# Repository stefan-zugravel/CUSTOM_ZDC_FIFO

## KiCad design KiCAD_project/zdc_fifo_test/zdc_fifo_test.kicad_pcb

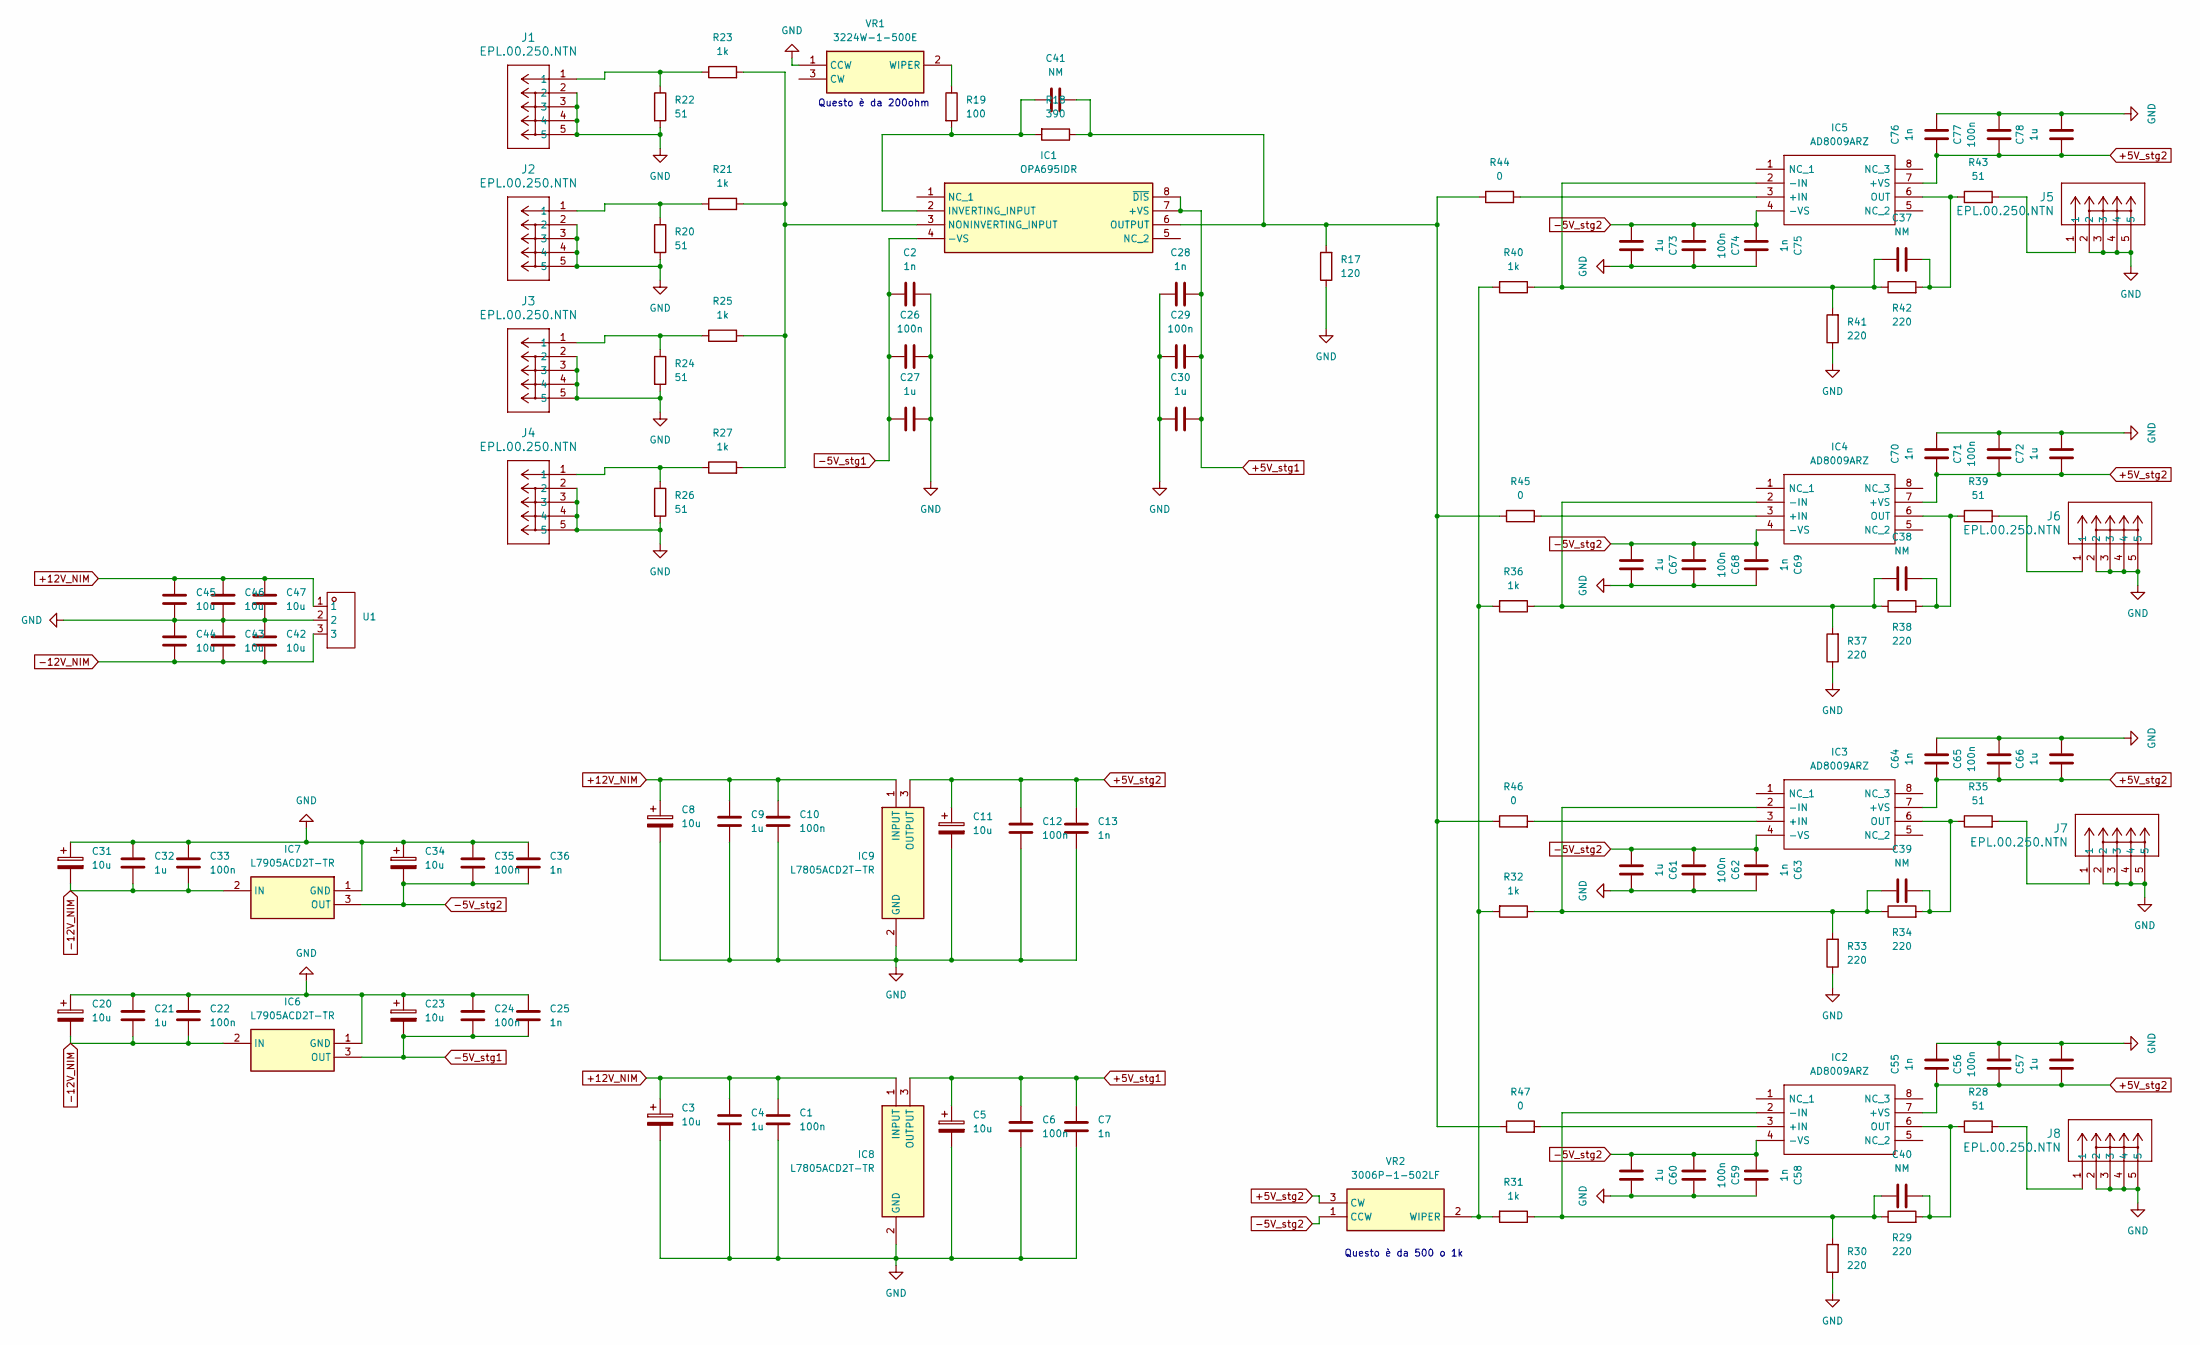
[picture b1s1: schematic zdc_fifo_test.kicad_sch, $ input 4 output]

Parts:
C1, C6, C10, C12, C22, C24, C26, C29, C33, C35, C56, C59, C62, C65, C68, C71, C74, C77: 100n; C_0402_1005Metric
C2, C7, C13, C25, C28, C36, C55, C58, C63, C64, C69, C70, C75, C76: 1n; C_0402_1005Metric
C3, C5, C8, C11, C31, C34, C42, C43, C44, C45, C46, C47: 10u; C_0805_2012Metric
C4, C9, C21, C30, C32, C57, C60, C61, C66, C67, C72, C73, C78: 1u; C_0603_1608Metric
C20: 10u; C_0805_2012Metric; JLCPCB C2836437
C23: 10u; C_0805_2012Metric; JLCPCB C15850
C27: 1u; C_0603_1608Metric; JLCPCB C15849
C37, C38, C39, C40, C41: NM; C_0402_1005Metric_Pad0.74x0.62mm_HandSolder
IC1: OPA695IDR; SOIC127P600X175-8N; Mouser Part Number 595-OPA695IDR
IC2, IC3, IC4, IC5: AD8009ARZ; SOIC127P600X175-8N; Mouser Part Number 584-AD8009ARZ
IC6, IC7: L7905ACD2T-TR; STB20N95K5; Mouser Part Number 511-L7905ACD2T-TR
IC8, IC9: L7805ACD2T-TR; L7805ACD2TTR; Mouser Part Number 511-L7805ACD2T-TR
J1, J2, J3, J4, J5, J6, J7, J8: EPL.00.250.NTN; CONN_EPK.00.250.NTN_LMO
R17: 120; R_0402_1005Metric
R18: 390; R_0603_1608Metric
R19: 100; R_0402_1005Metric
R20, R22, R24, R26, R28, R35, R39, R43: 51; R_0603_1608Metric
R21, R23, R25, R27, R31, R32, R36, R40: 1k; R_0402_1005Metric
R29, R30, R33, R34, R37, R38, R41, R42: 220; R_0402_1005Metric
R44, R45, R46, R47: 0; R_0603_1608Metric_Pad0.98x0.95mm_HandSolder
U1: CONN-TH_XY126V-5.0-3P; Manufacturer Part XY126V-5.0-3P; LCSC Part Name 1x3P 5mm 直插 排数:1 每排P数:3
VR1: 3224W-1-500E; 3224W1500E; Mouser Part Number 652-3224W-1-500E
VR2: 3006P-1-502LF; 3006P_1; Mouser Part Number 652-3006P-1-502-LF

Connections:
+5V_stg1: C5.1, C6.1, C7.1, C28.1, C29.1, C30.1, IC1.7 (+VS), IC1.8 (~DIS), IC8.3 (OUTPUT)
+5V_stg2: C11.1, C12.1, C13.1, C55.1, C56.1, C57.1, C64.1, C65.1, C66.1, C70.1, C71.1, C72.1, C76.1, C77.1, C78.1, IC2.7 (+VS), IC3.7 (+VS), IC4.7 (+VS), IC5.7 (+VS), IC9.3 (OUTPUT), VR2.3 (CW)
+12V_NIM: C1.1, C3.1, C4.1, C8.1, C9.1, C10.1, C45.1, C46.1, C47.1, IC8.1 (INPUT), IC9.1 (INPUT), U1.1
-5V_stg1: C2.1, C23.2, C24.2, C25.2, C26.1, C27.1, IC1.4 (-VS), IC6.3 (OUT)
-5V_stg2: C34.2, C35.2, C36.2, C58.1, C59.1, C60.1, C61.1, C62.1, C63.1, C67.1, C68.1, C69.1, C73.1, C74.1, C75.1, IC2.4 (-VS), IC3.4 (-VS), IC4.4 (-VS), IC5.4 (-VS), IC7.3 (OUT), VR2.1 (CCW)
-12V_NIM: C20.2, C21.2, C22.2, C31.2, C32.2, C33.2, C42.2, C43.2, C44.2, IC6.2 (IN), IC7.2 (IN), U1.3
GND: C1.2, C2.2, C3.2, C4.2, C5.2, C6.2, C7.2, C8.2, C9.2, C10.2, C11.2, C12.2, C13.2, C20.1, C21.1, C22.1, C23.1, C24.1, C25.1, C26.2, C27.2, C28.2, C29.2, C30.2, C31.1, C32.1, C33.1, C34.1, C35.1, C36.1, C42.1, C43.1, C44.1, C45.2, C46.2, C47.2, C55.2, C56.2, C57.2, C58.2, C59.2, C60.2, C61.2, C62.2, C63.2, C64.2, C65.2, C66.2, C67.2, C68.2, C69.2, C70.2, C71.2, C72.2, C73.2, C74.2, C75.2, C76.2, C77.2, C78.2, IC6.1 (GND), IC7.1 (GND), IC8.2 (GND), IC9.2 (GND), J1.2, J1.3, J1.4, J1.5, J2.2, J2.3, J2.4, J2.5, J3.2, J3.3, J3.4, J3.5, J4.2, J4.3, J4.4, J4.5, J5.2, J5.3, J5.4, J5.5, J6.2, J6.3, J6.4, J6.5, J7.2, J7.3, J7.4, J7.5, J8.2, J8.3, J8.4, J8.5, R17.1, R20.2, R22.2, R24.2, R26.2, R30.1, R33.1, R37.1, R41.1, U1.2, VR1.1 (CCW)
unnamed: C41.2, IC1.2 (INVERTING_INPUT), R18.2, R19.2
unnamed: IC1.3 (NONINVERTING_INPUT), R21.2, R23.2, R25.2, R27.2
unnamed: C41.1, IC1.6 (OUTPUT), R17.2, R18.1, R44.1, R45.1, R46.1, R47.1
unnamed: IC2.3 (+IN), R47.2
unnamed: C40.2, IC2.2 (-IN), R29.1, R30.2, R31.1
unnamed: C40.1, IC2.6 (OUT), R28.1, R29.2
unnamed: IC3.3 (+IN), R46.2
unnamed: C39.2, IC3.2 (-IN), R32.1, R33.2, R34.1
unnamed: C39.1, IC3.6 (OUT), R34.2, R35.1
unnamed: IC4.3 (+IN), R45.2
unnamed: C38.2, IC4.2 (-IN), R36.1, R37.2, R38.1
unnamed: C38.1, IC4.6 (OUT), R38.2, R39.1
unnamed: IC5.3 (+IN), R44.2
unnamed: C37.2, IC5.2 (-IN), R40.1, R41.2, R42.1
unnamed: C37.1, IC5.6 (OUT), R42.2, R43.1
unnamed: J1.1, R22.1, R23.1
unnamed: J2.1, R20.1, R21.1
unnamed: J3.1, R24.1, R25.1
unnamed: J4.1, R26.1, R27.1
unnamed: J5.1, R43.2
unnamed: J6.1, R39.2
unnamed: J7.1, R35.2
unnamed: J8.1, R28.2
unnamed: R19.1, VR1.2 (WIPER)
unnamed: R31.2, R32.2, R36.2, R40.2, VR2.2 (WIPER)

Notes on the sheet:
Questo è da 200ohm
Questo è da 500 o 1k

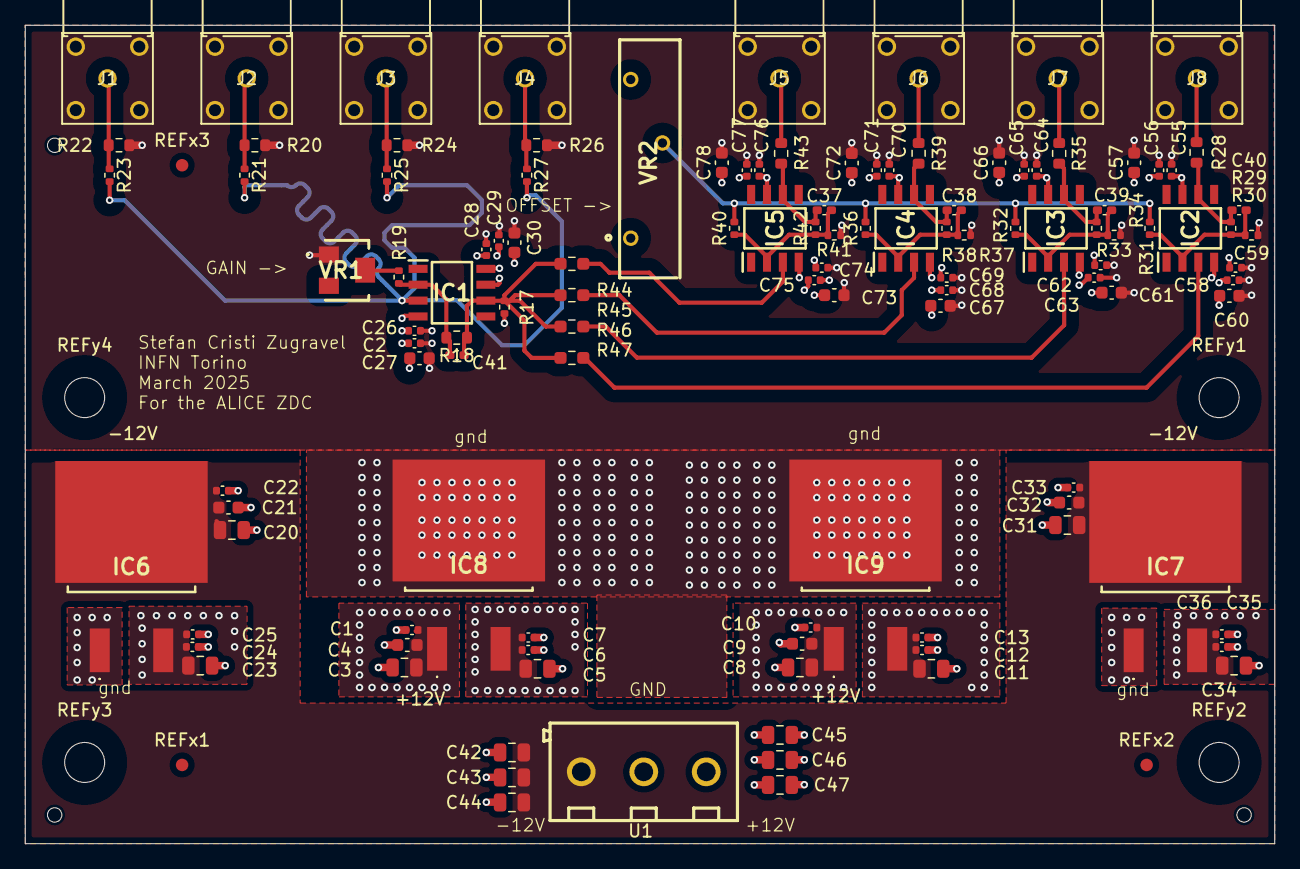
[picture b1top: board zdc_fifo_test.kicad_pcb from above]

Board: 6 copper layers, 100.0 x 65.5 mm, 123 parts (0 on the bottom side), 32 nets.

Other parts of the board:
REFx1, REFx2, REFx3: Fiducial_1mm_Mask2mm
REFy1, REFy2, REFy3, REFy4: MountingHole_3.2mm_M3

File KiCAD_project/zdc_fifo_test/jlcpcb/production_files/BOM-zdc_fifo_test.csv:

Comment,Designator,Footprint,LCSC,Quantity
3224W-1-500E,VR1,3224W1500E,C116321,1
1k,"R21,R23,R25,R27,R31,R32,R36,R40",R_0402_1005Metric,C11702,8
3006P-1-502LF,VR2,3006P_1,C118914,1
1n,"C13,C2,C25,C28,C36,C55,C58,C63,C64,C69,C7,C70,C75,C76",C_0402_1005Metric,C1523,14
1u,"C21,C27,C30,C32,C4,C57,C60,C61,C66,C67,C72,C73,C78,C9",C_0603_1608Metric,C15849,14
10u,"C11,C20,C23,C3,C31,C34,C42,C43,C44,C45,C46,C47,C5,C8",C_0805_2012Metric,C15850,14
OPA695IDR,IC1,SOIC127P600X175-8N,C1848175,1
0,"R44,R45,R46,R47",R_0603_1608Metric_Pad0.98x0.95mm_HandSolder,C21189,4
390,R18,R_0603_1608Metric,C23151,1
51,"R20,R22,R24,R26,R28,R35,R39,R43",R_0603_1608Metric,C23197,8
100,R19,R_0402_1005Metric,C25076,1
120,R17,R_0402_1005Metric,C25079,1
220,"R29,R30,R33,R34,R37,R38,R41,R42",R_0402_1005Metric,C25091,8
L7905ACD2T-TR,"IC6,IC7",STB20N95K5,C2943060,2
100n,"C1,C10,C12,C22,C24,C26,C29,C33,C35,C56,C59,C6,C62,C65,C68,C71,C74,C77",C_0402_1005Metric,C307331,18
L7805ACD2T-TR,"IC8,IC9",L7805ACD2TTR,C53236,2
~,U1,CONN-TH_XY126V-5.0-3P,C557647,1
AD8009ARZ,"IC2,IC3,IC4,IC5",SOIC127P600X175-8N,C652162,4

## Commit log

2025-03-05 init
2025-03-05 design 1
2025-03-06 inverting design
2025-03-06 good non inverting design
2025-03-06 added kicad project
2025-03-07 added KiCAD project and ad8009 config
2025-03-09 Started PCB layout
2025-03-11 first gerber generated
2025-03-11 Added updated BOM files and gerber
2025-03-12 cleaned up files
2025-03-12 added slides material
2025-03-17 v0.1 -> JLCPCB order
2025-03-18 Test with ngspice
2025-03-28 sim oscillation
